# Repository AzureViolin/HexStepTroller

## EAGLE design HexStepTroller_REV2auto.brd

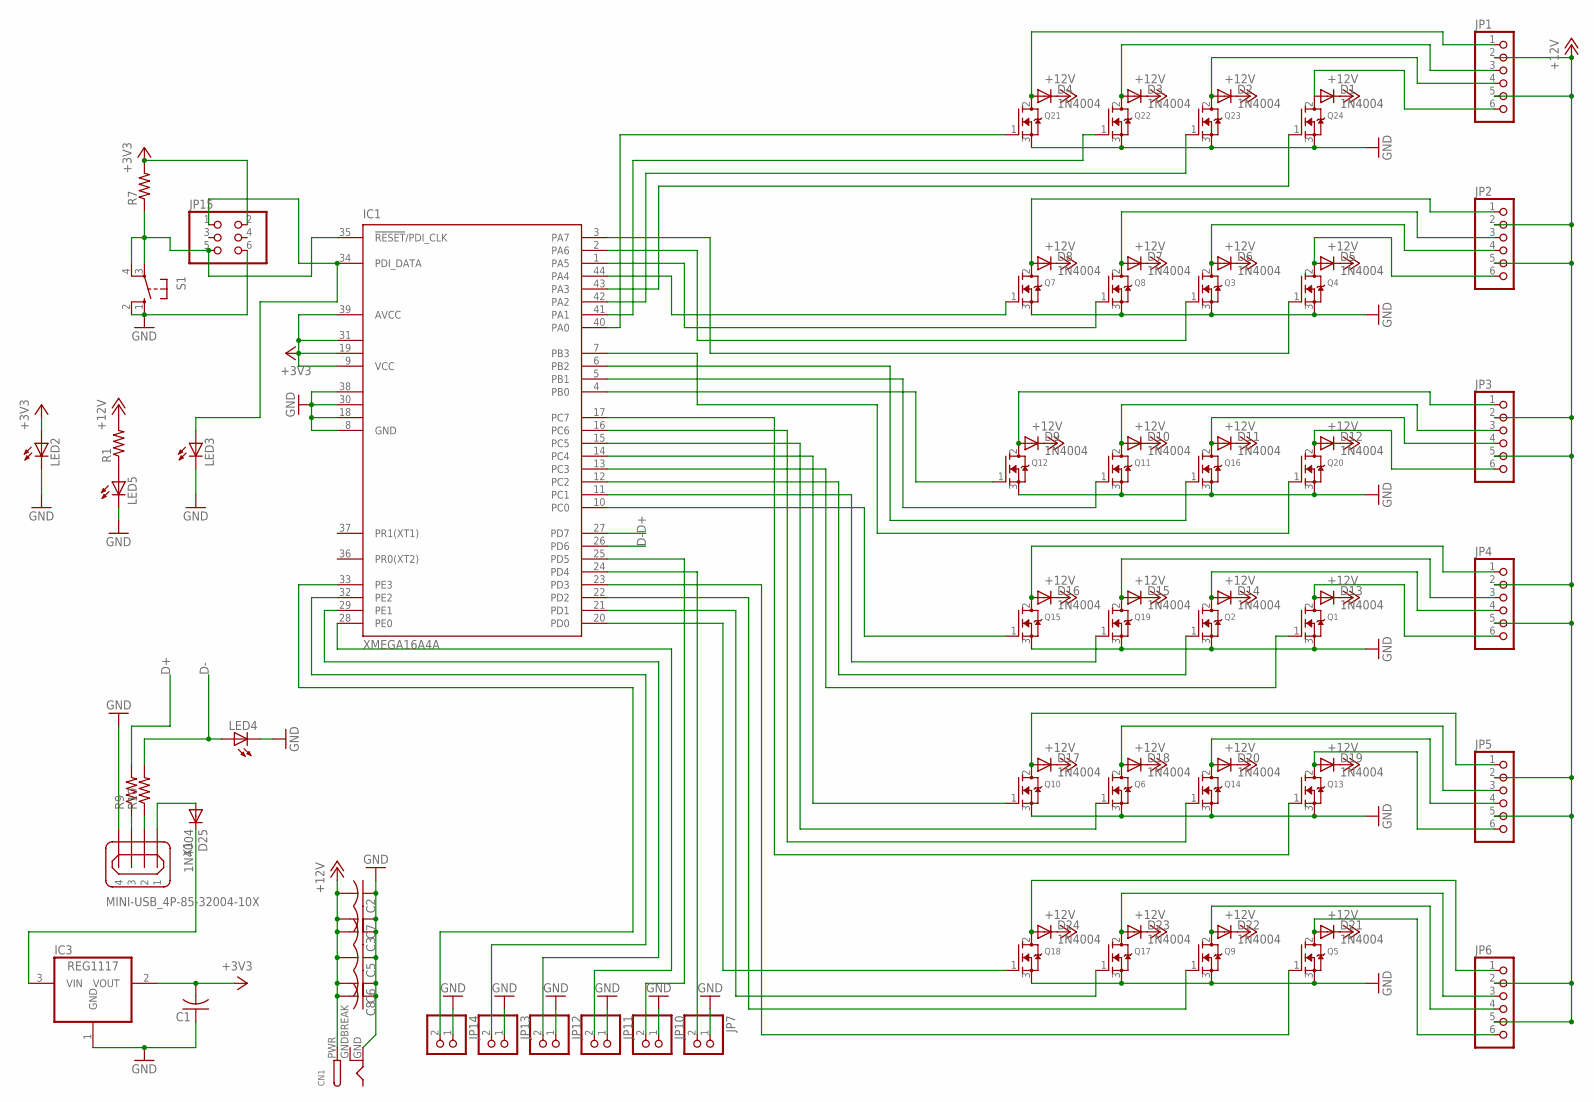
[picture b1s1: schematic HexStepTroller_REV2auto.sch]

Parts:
C1, C2, C3, C5, C6, C7, C8: C-US050-075X075; C050-075X075
CN1: DCBARRELPTH; DCJACK_2MM_PTH
D1, D2, D3, D4, D5, D6, D7, D8, D9, D10, D11, D12, D13, D14, D15, D16, D17, D18, D19, D20, D21, D22, D23, D24, D25: 1N4004; DO41-10
IC1: XMEGA16A4A; TQFP44
IC3: REG1117; SOT223
JP1, JP2, JP3, JP4, JP5, JP6: PINHD-1X6; 1X06
JP7, JP10, JP11, JP12, JP13, JP14: PINHD-1X2; 1X02
JP15: PINHD-2X3; 2X03
LED2, LED3, LED4, LED5: LED5MM
Q1, Q2, Q3, Q4, Q5, Q6, Q7, Q8, Q9, Q10, Q11, Q12, Q13, Q14, Q15, Q16, Q17, Q18, Q19, Q20, Q21, Q22, Q23, Q24: MOSFET-NGDS_TO220V; TO220V
R1, R7, R9, R10: R-US_0204/7; 0204/7
S1: 10-XX; B3F-10XX
X1: MINI-USB_4P-85-32004-10X; 85-32004-10X

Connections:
+3V3: C1.2, IC1.9 (VCC), IC1.19 (VCC1), IC1.31 (VCC2), IC1.39 (AVCC), IC3.2 (VOUT), JP15.2, LED2.A, R7.2
+12V: C2.2, C3.2, C5.2, C6.2, C7.2, C8.2, CN1.PWR, D1.C, D2.C, D3.C, D4.C, D5.C, D6.C, D7.C, D8.C, D9.C, D10.C, D11.C, D12.C, D13.C, D14.C, D15.C, D16.C, D17.C, D18.C, D19.C, D20.C, D21.C, D22.C, D23.C, D24.C, JP1.2, JP1.5, JP2.2, JP2.5, JP3.2, JP3.5, JP4.2, JP4.5, JP5.2, JP5.5, JP6.2, JP6.5, R1.2
D+: IC1.27 (PD7), R9.2
D-: IC1.26 (PD6), LED4.A, R10.2
GND: C1.1, C2.1, C3.1, C5.1, C6.1, C7.1, C8.1, CN1.GND, IC1.8 (GND), IC1.18 (GND1), IC1.30 (GND2), IC1.38 (GND3), IC3.1 (GND), JP7.1, JP10.1, JP11.1, JP12.1, JP13.1, JP14.1, JP15.6, LED2.K (C), LED3.K (C), LED4.K (C), LED5.K (C), Q1.3 (S), Q2.3 (S), Q3.3 (S), Q4.3 (S), Q5.3 (S), Q6.3 (S), Q7.3 (S), Q8.3 (S), Q9.3 (S), Q10.3 (S), Q11.3 (S), Q12.3 (S), Q13.3 (S), Q14.3 (S), Q15.3 (S), Q16.3 (S), Q17.3 (S), Q18.3 (S), Q19.3 (S), Q20.3 (S), Q21.3 (S), Q22.3 (S), Q23.3 (S), Q24.3 (S), S1.1 (S), S1.2 (S1), X1.4
GNDBREAK: CN1.GNDBREAK
unnamed: D1.A, JP1.6, Q24.2 (D)
unnamed: D2.A, JP1.4, Q23.2 (D)
unnamed: D3.A, JP1.3, Q22.2 (D)
unnamed: D4.A, JP1.1, Q21.2 (D)
unnamed: D5.A, JP2.6, Q4.2 (D)
unnamed: D6.A, JP2.4, Q3.2 (D)
unnamed: D7.A, JP2.3, Q8.2 (D)
unnamed: D8.A, JP2.1, Q7.2 (D)
unnamed: D9.A, JP3.1, Q12.2 (D)
unnamed: D10.A, JP3.3, Q11.2 (D)
unnamed: D11.A, JP3.4, Q16.2 (D)
unnamed: D12.A, JP3.6, Q20.2 (D)
unnamed: D13.A, JP4.6, Q1.2 (D)
unnamed: D14.A, JP4.4, Q2.2 (D)
unnamed: D15.A, JP4.3, Q19.2 (D)
unnamed: D16.A, JP4.1, Q15.2 (D)
unnamed: D17.A, JP5.1, Q10.2 (D)
unnamed: D18.A, JP5.3, Q6.2 (D)
unnamed: D19.A, JP5.6, Q13.2 (D)
unnamed: D20.A, JP5.4, Q14.2 (D)
unnamed: D21.A, JP6.6, Q5.2 (D)
unnamed: D22.A, JP6.4, Q9.2 (D)
unnamed: D23.A, JP6.3, Q17.2 (D)
unnamed: D24.A, JP6.1, Q18.2 (D)
unnamed: IC1.44 (PA4), Q7.1 (G)
unnamed: IC1.25 (PD5), JP10.2
unnamed: IC1.28 (PE0), JP11.2
unnamed: LED5.A, R1.1
unnamed: IC1.32 (PE2), JP13.2
unnamed: IC1.33 (PE3), JP14.2
unnamed: IC1.35 (!RESET!/PDI_CLK), JP15.5, R7.1, S1.3, S1.4 (P1)
unnamed: D25.C, IC3.3 (VIN)
unnamed: R9.1, X1.3
unnamed: D25.A, X1.1
unnamed: IC1.34 (PDI_DATA), JP15.1, LED3.A
unnamed: IC1.24 (PD4), JP7.2
unnamed: IC1.29 (PE1), JP12.2
unnamed: R10.1, X1.2
unnamed: IC1.40 (PA0), Q21.1 (G)
unnamed: IC1.41 (PA1), Q22.1 (G)
unnamed: IC1.42 (PA2), Q23.1 (G)
unnamed: IC1.43 (PA3), Q24.1 (G)
unnamed: IC1.1 (PA5), Q8.1 (G)
unnamed: IC1.2 (PA6), Q3.1 (G)
unnamed: IC1.3 (PA7), Q4.1 (G)
unnamed: IC1.4 (PB0), Q12.1 (G)
unnamed: IC1.5 (PB1), Q11.1 (G)
unnamed: IC1.6 (PB2), Q16.1 (G)
unnamed: IC1.7 (PB3), Q20.1 (G)
unnamed: IC1.10 (PC0), Q15.1 (G)
unnamed: IC1.11 (PC1), Q19.1 (G)
unnamed: IC1.12 (PC2), Q2.1 (G)
unnamed: IC1.13 (PC3), Q1.1 (G)
unnamed: IC1.14 (PC4), Q10.1 (G)
unnamed: IC1.15 (PC5), Q6.1 (G)
unnamed: IC1.16 (PC6), Q14.1 (G)
unnamed: IC1.17 (PC7), Q13.1 (G)
unnamed: IC1.20 (PD0), Q18.1 (G)
unnamed: IC1.21 (PD1), Q17.1 (G)
unnamed: IC1.22 (PD2), Q9.1 (G)
unnamed: IC1.23 (PD3), Q5.1 (G)

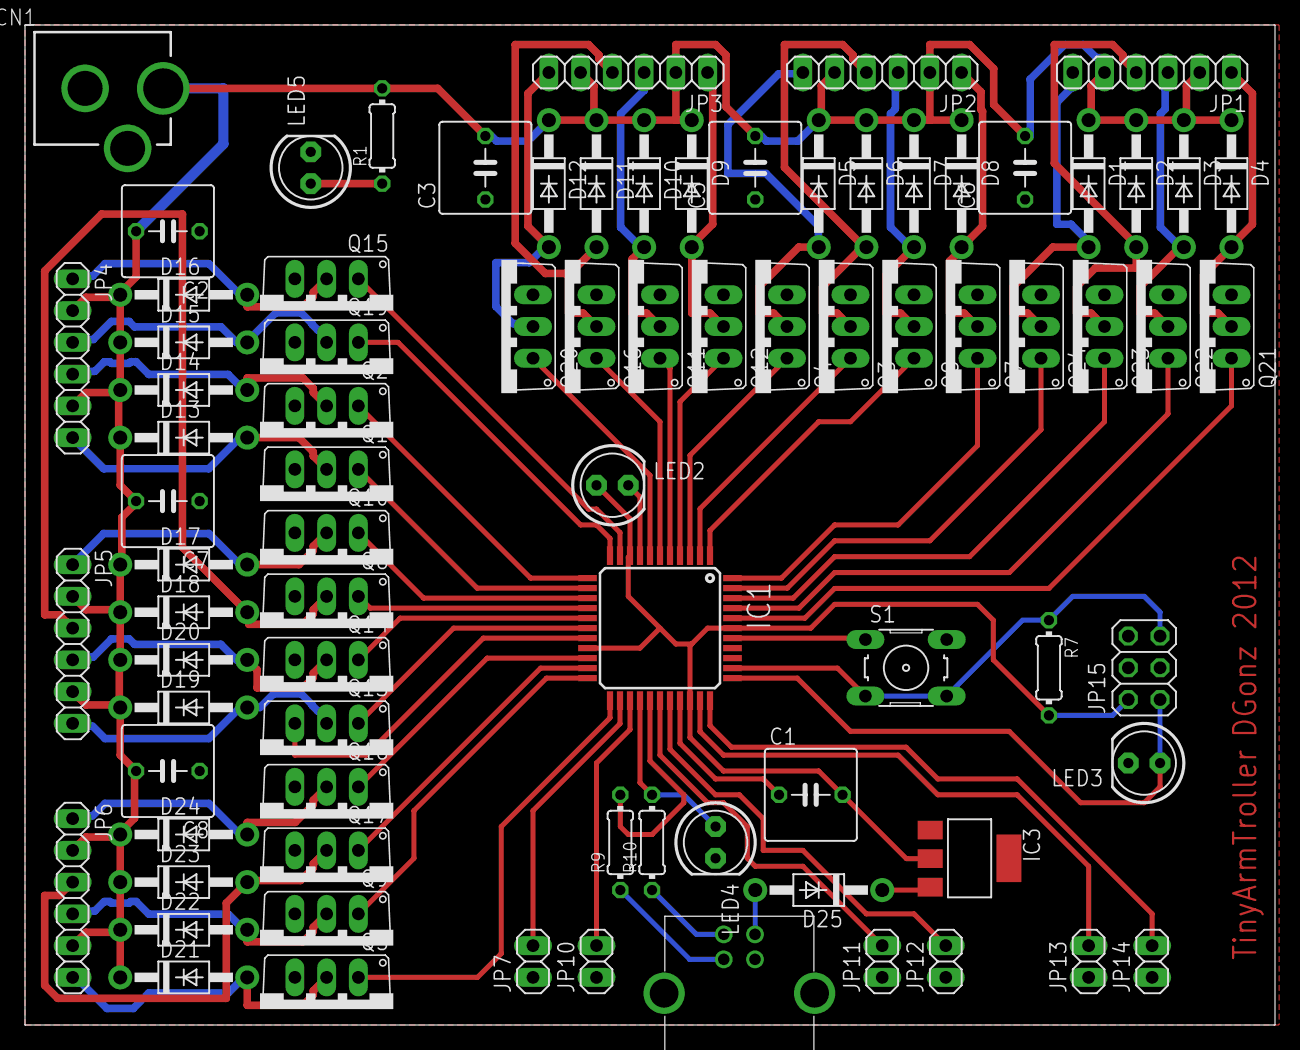
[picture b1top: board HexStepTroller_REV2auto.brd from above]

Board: 2 copper layers, 100.0 x 80.0 mm, 82 parts (0 on the bottom side), 66 nets.

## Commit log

2012-07-23 basic done, except time
